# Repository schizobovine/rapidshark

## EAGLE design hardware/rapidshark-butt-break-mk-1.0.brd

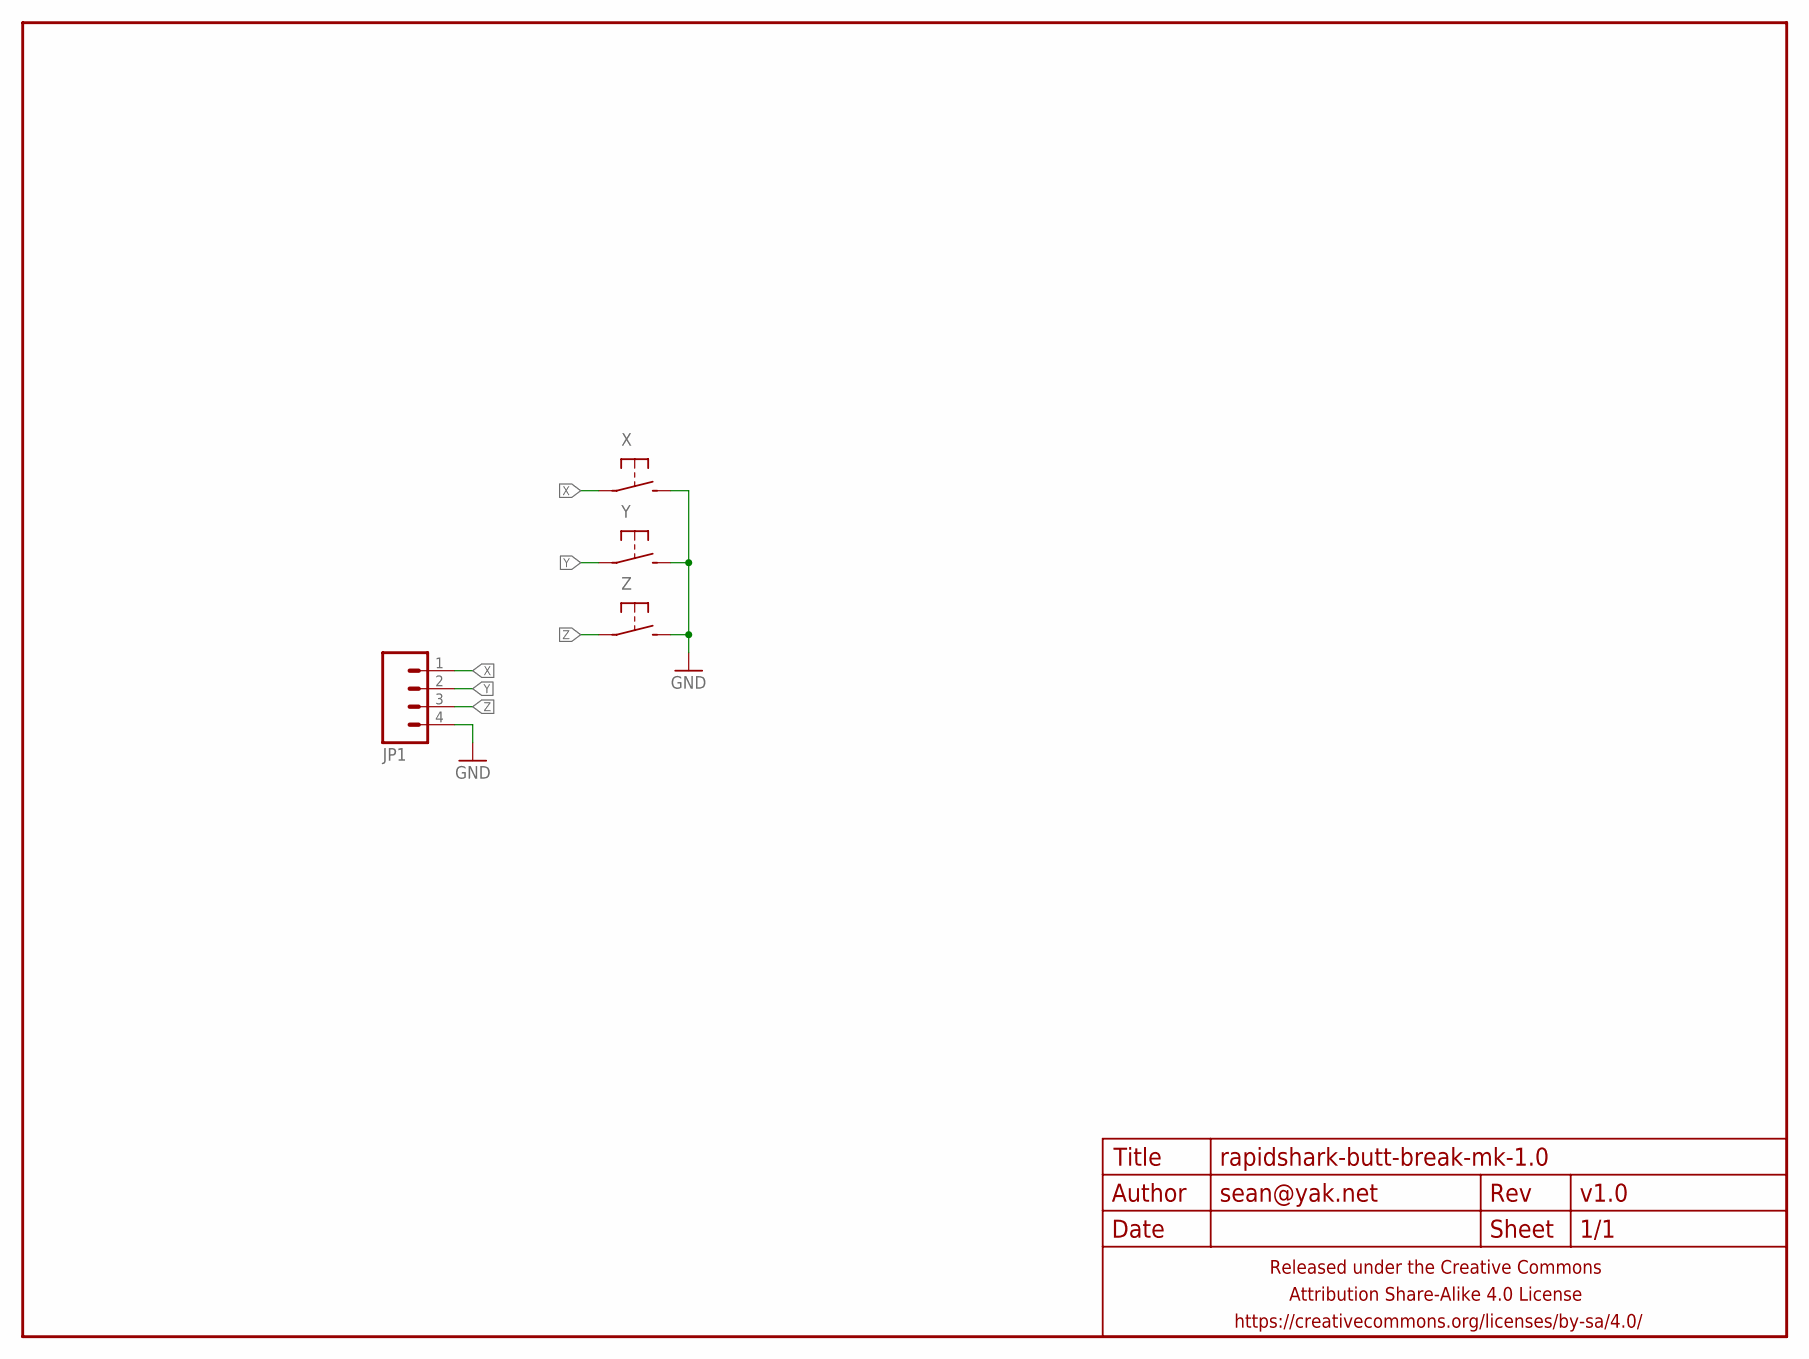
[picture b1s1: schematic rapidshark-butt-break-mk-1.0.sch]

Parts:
FRAME1: FRAME-LETTERNO_PACKAGE; DUMMY
JP1: M04JST-PTH; JST-4-PH-RA-PTH
X: SPST-NO-TACT3MM-PTH-SMALL-PADS; DTS-3-SMALL-PADS
Y: SPST-NO-TACT3MM-PTH-SMALL-PADS; DTS-3-SMALL-PADS
Z: SPST-NO-TACT3MM-PTH-SMALL-PADS; DTS-3-SMALL-PADS

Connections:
GND: JP1.4, X.2, Y.2, Z.2
X: JP1.1, X.1
Y: JP1.2, Y.1
Z: JP1.3, Z.1

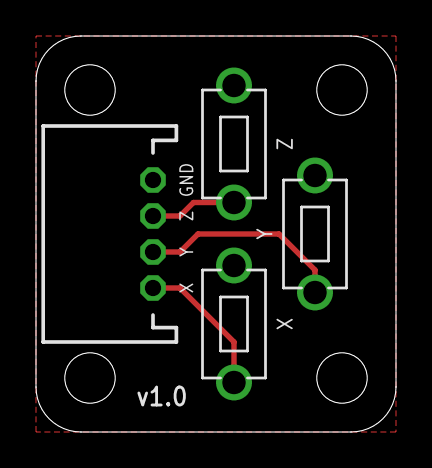
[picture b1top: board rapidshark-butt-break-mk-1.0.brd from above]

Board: 2 copper layers, 20.0 x 22.0 mm, 5 parts (1 on the bottom side), 4 nets.

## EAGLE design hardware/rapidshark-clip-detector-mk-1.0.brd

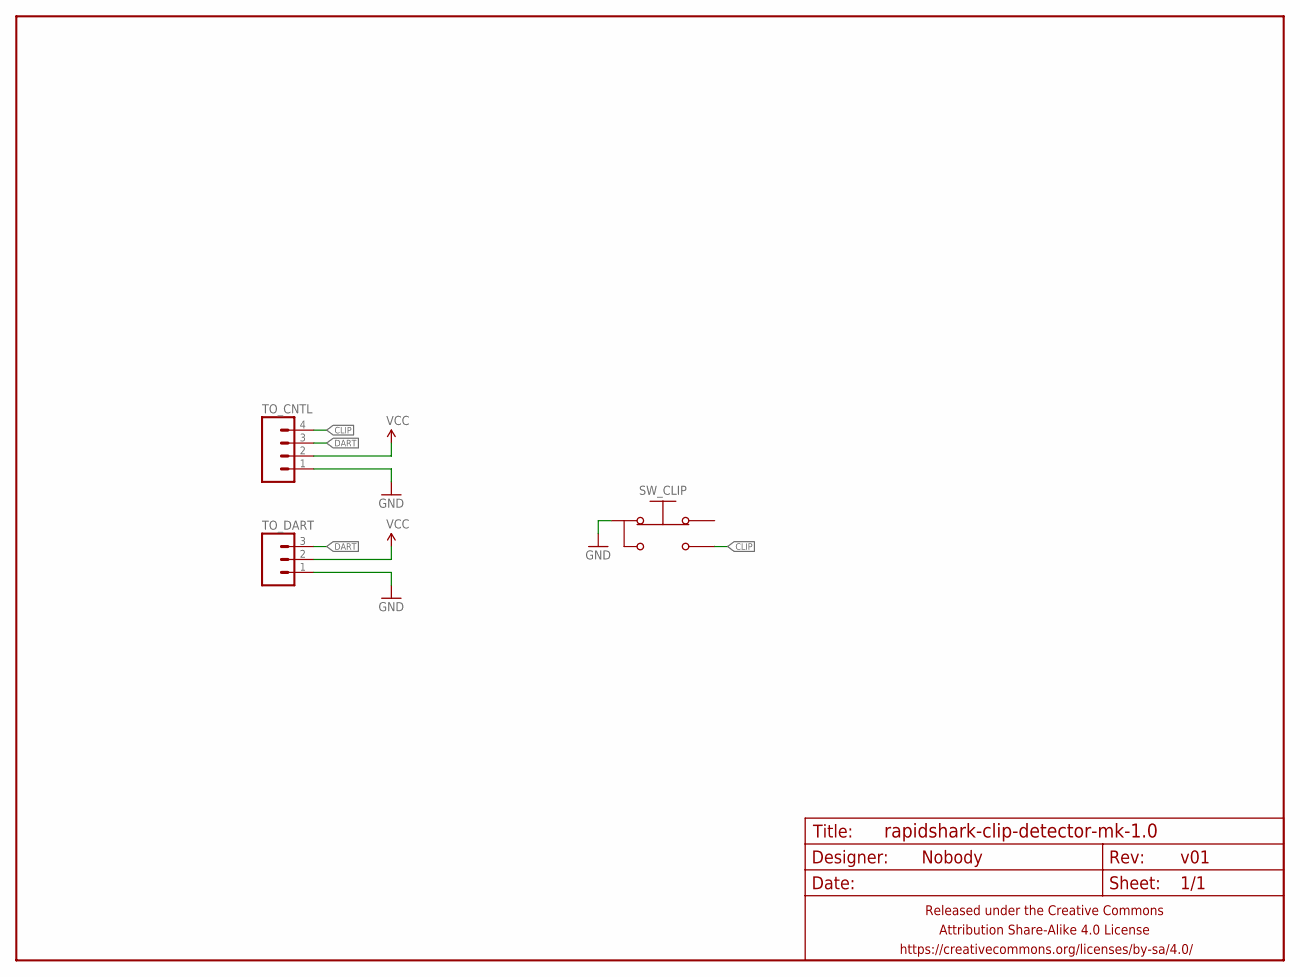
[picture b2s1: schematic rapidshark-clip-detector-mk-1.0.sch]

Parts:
FRAME1: FRAME-LETTERNO_PACKAGE; DUMMY
SW_CLIP: SPDT-NO-TACTPTH-RA-DETECT-3MM; SWITCH-DETECH-SPDT-3MM
TO_CNTL: M04JST-PTH-VERT; JST-4-PH-VERT-PTH
TO_DART: M03JST-PTH-VERT; JST-3-PH-VERT-PTH

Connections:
CLIP: SW_CLIP.3 (NO), TO_CNTL.4
DART: TO_CNTL.3, TO_DART.3
GND: SW_CLIP.2 (COM), TO_CNTL.1, TO_DART.1
VCC: TO_CNTL.2, TO_DART.2

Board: 2 copper layers, 4 parts (2 on the bottom side), 4 nets, no tracks yet.

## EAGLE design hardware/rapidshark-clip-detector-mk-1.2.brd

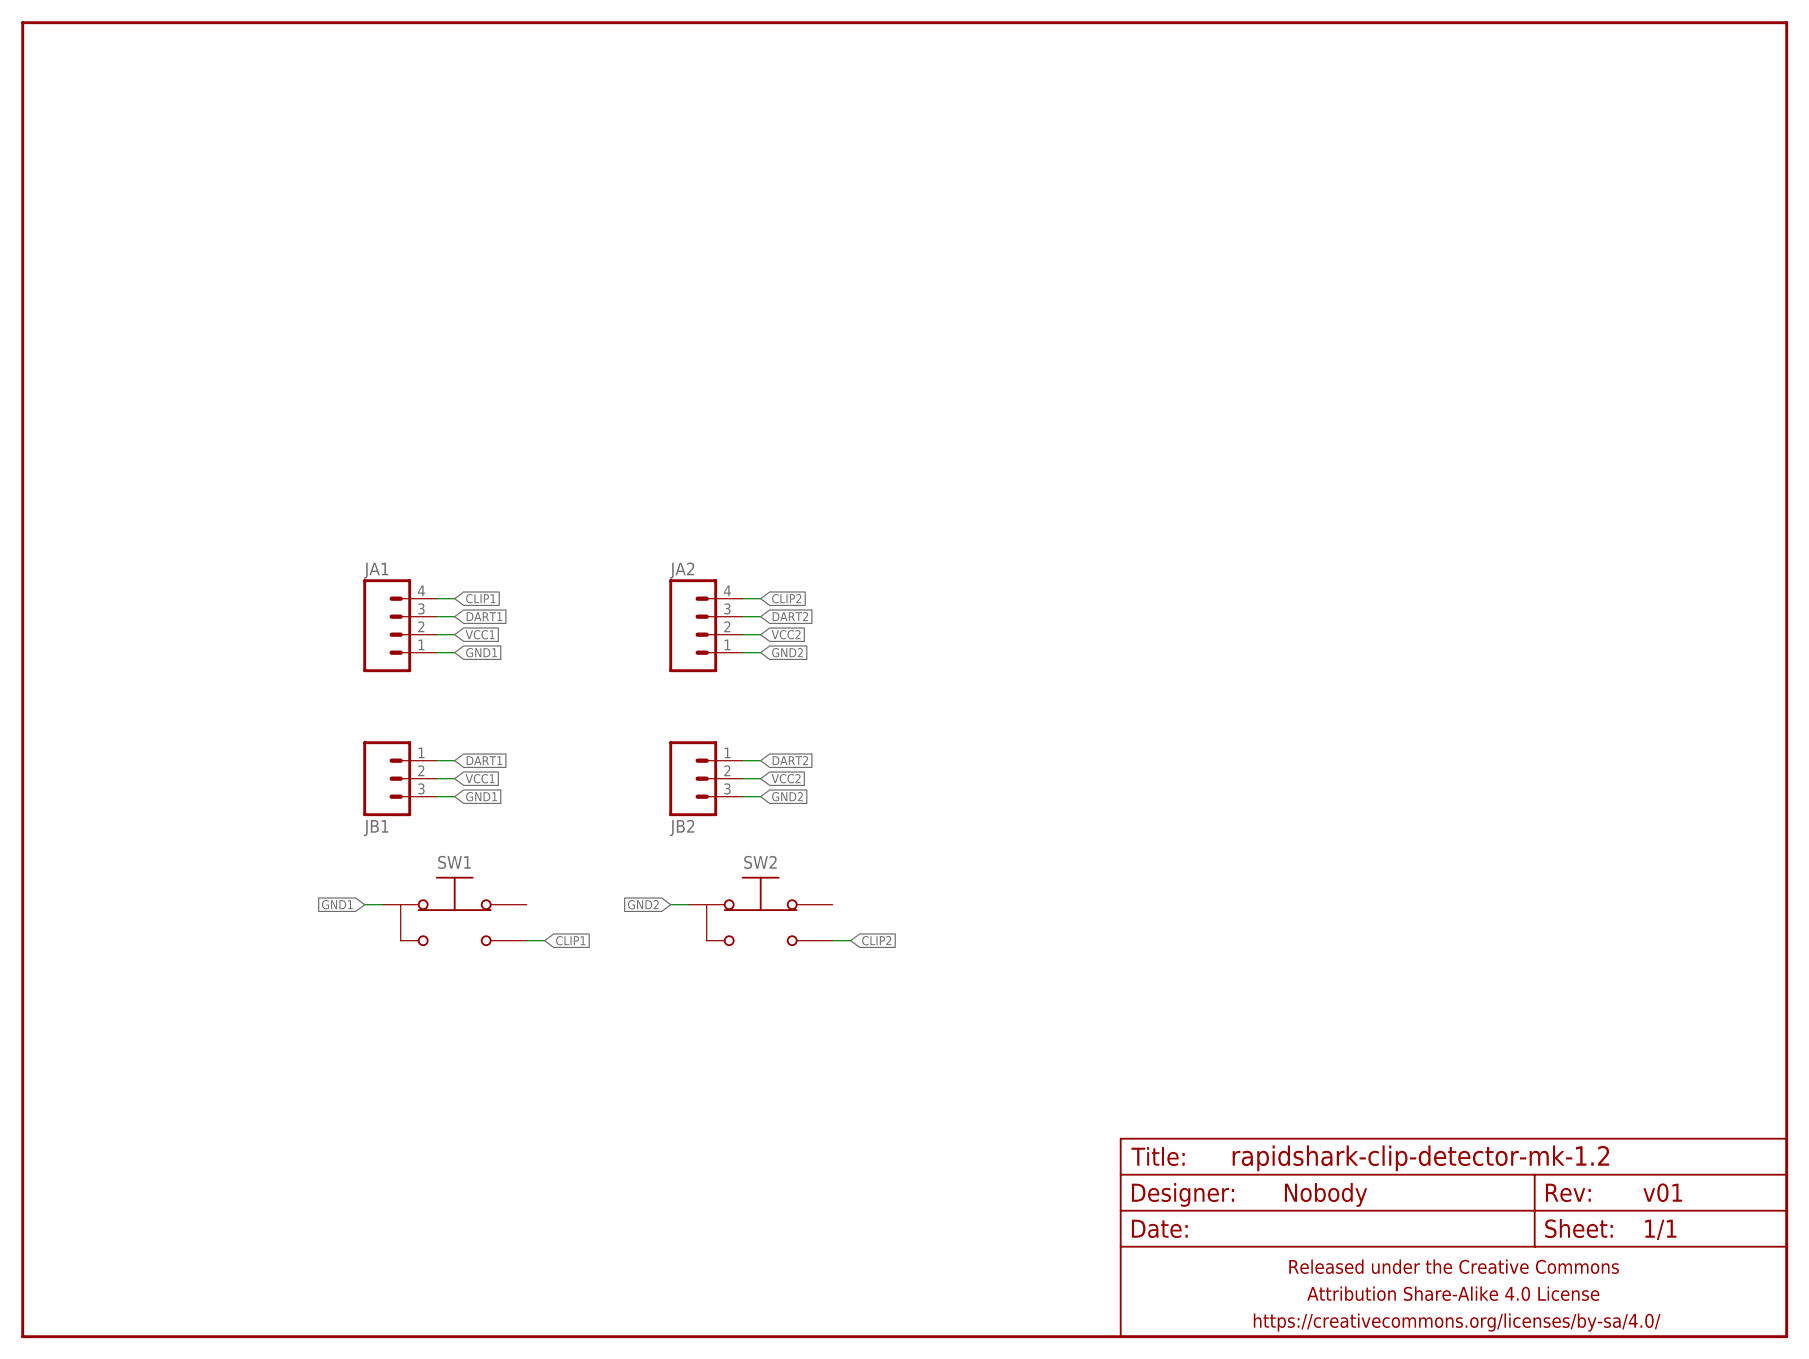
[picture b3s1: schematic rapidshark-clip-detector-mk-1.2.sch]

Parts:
FRAME1: FRAME-LETTERNO_PACKAGE; DUMMY
JA1, JA2: M04JST-PTH-VERT; JST-4-PH-VERT-PTH
JB1, JB2: M03JST-PTH-VERT; JST-3-PH-VERT-PTH
SW1, SW2: SPDT-NO-TACTPTH-RA-DETECT-3MM; SWITCH-DETECH-SPDT-3MM

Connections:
CLIP1: JA1.4, SW1.3 (NO)
CLIP2: JA2.4, SW2.3 (NO)
DART1: JA1.3, JB1.1
DART2: JA2.3, JB2.1
GND1: JA1.1, JB1.3, SW1.2 (COM)
GND2: JA2.1, JB2.3, SW2.2 (COM)
VCC1: JA1.2, JB1.2
VCC2: JA2.2, JB2.2

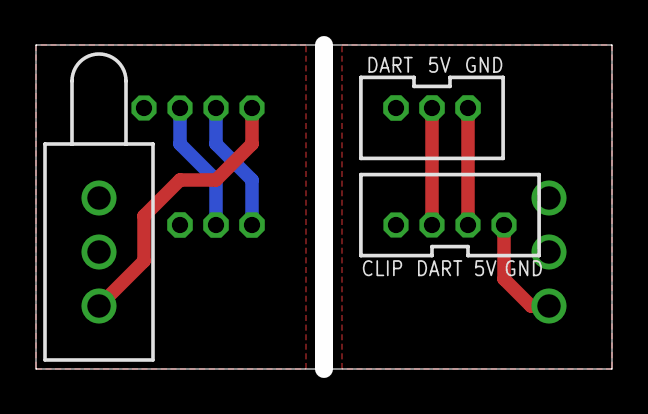
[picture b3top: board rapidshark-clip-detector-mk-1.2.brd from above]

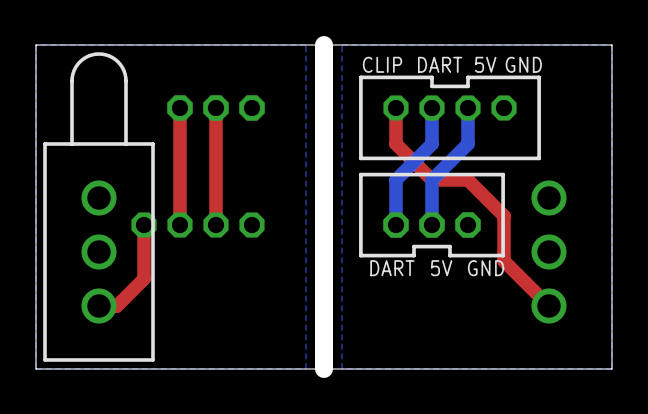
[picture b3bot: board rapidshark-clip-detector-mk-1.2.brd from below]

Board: 2 copper layers, 32.0 x 18.0 mm, 7 parts (4 on the bottom side), 8 nets.

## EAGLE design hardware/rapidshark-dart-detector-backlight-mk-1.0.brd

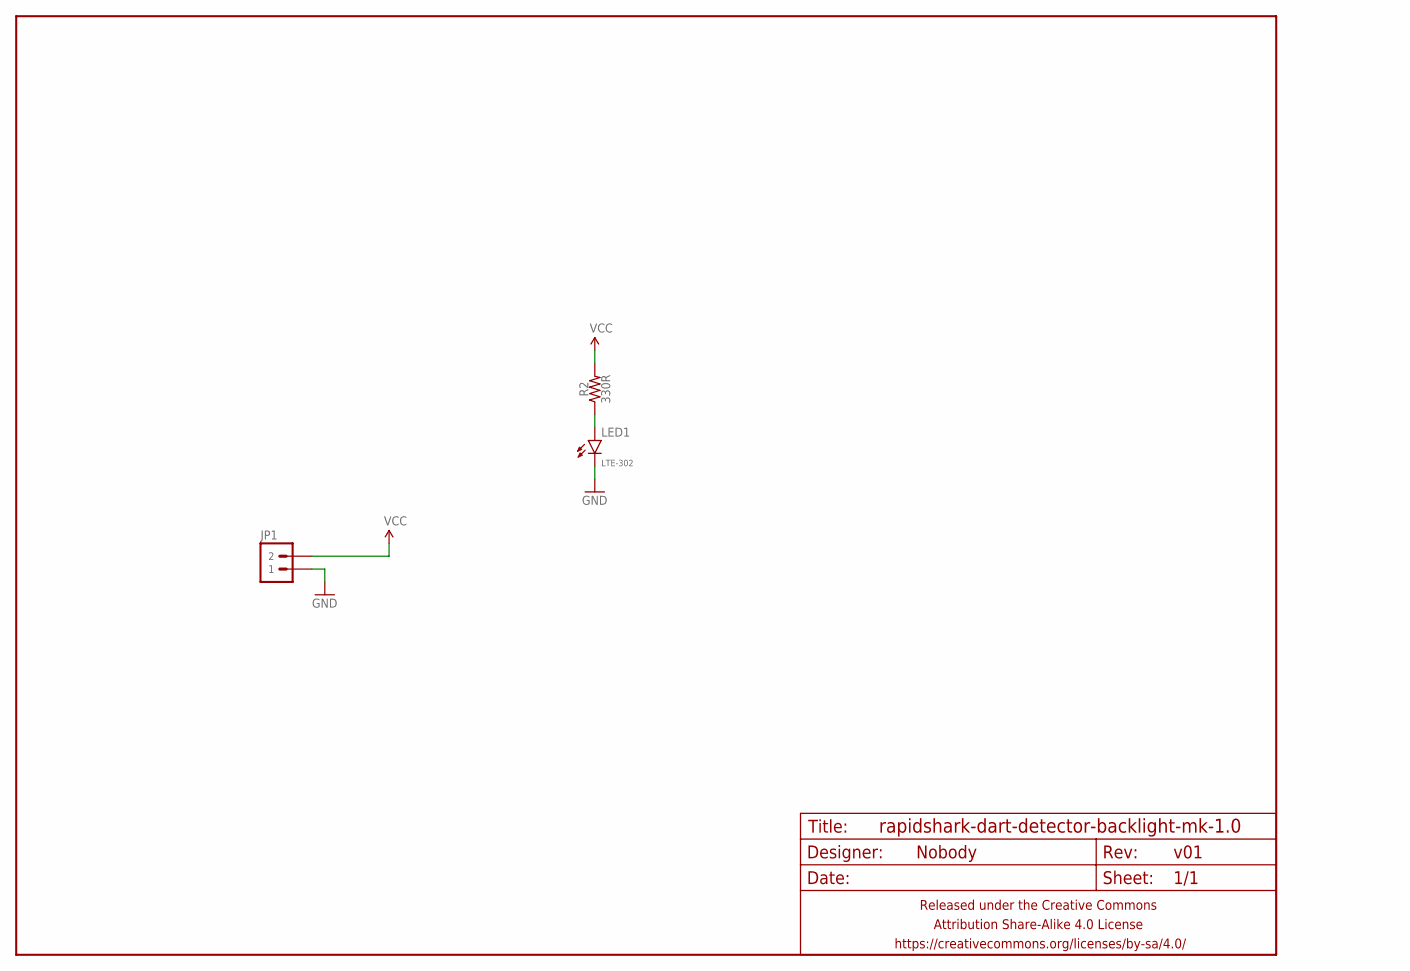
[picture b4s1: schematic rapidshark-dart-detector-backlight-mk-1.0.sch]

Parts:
FRAME1: FRAME-LETTERNO_PACKAGE; DUMMY
JP1: M02JST-PTH-RA-R+; JST-2-PH-RA-PTH-R+
LED1: LTE-302; LED-2.54MM-SIDE
R2: 330R; RESISTOR-AXIAL-PTH-7.62MM

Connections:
GND: JP1.1, LED1.K (C)
unnamed: LED1.A, R2.P$1 (1)
VCC: JP1.2, R2.P$2 (2)

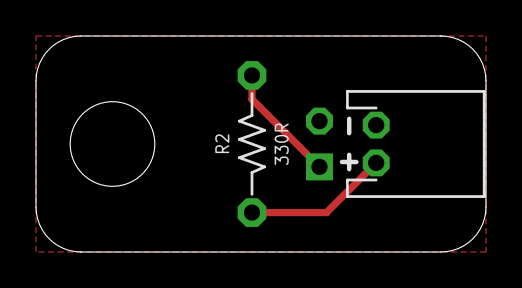
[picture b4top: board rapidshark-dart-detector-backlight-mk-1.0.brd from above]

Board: 2 copper layers, 25.0 x 12.0 mm, 4 parts (1 on the bottom side), 3 nets.

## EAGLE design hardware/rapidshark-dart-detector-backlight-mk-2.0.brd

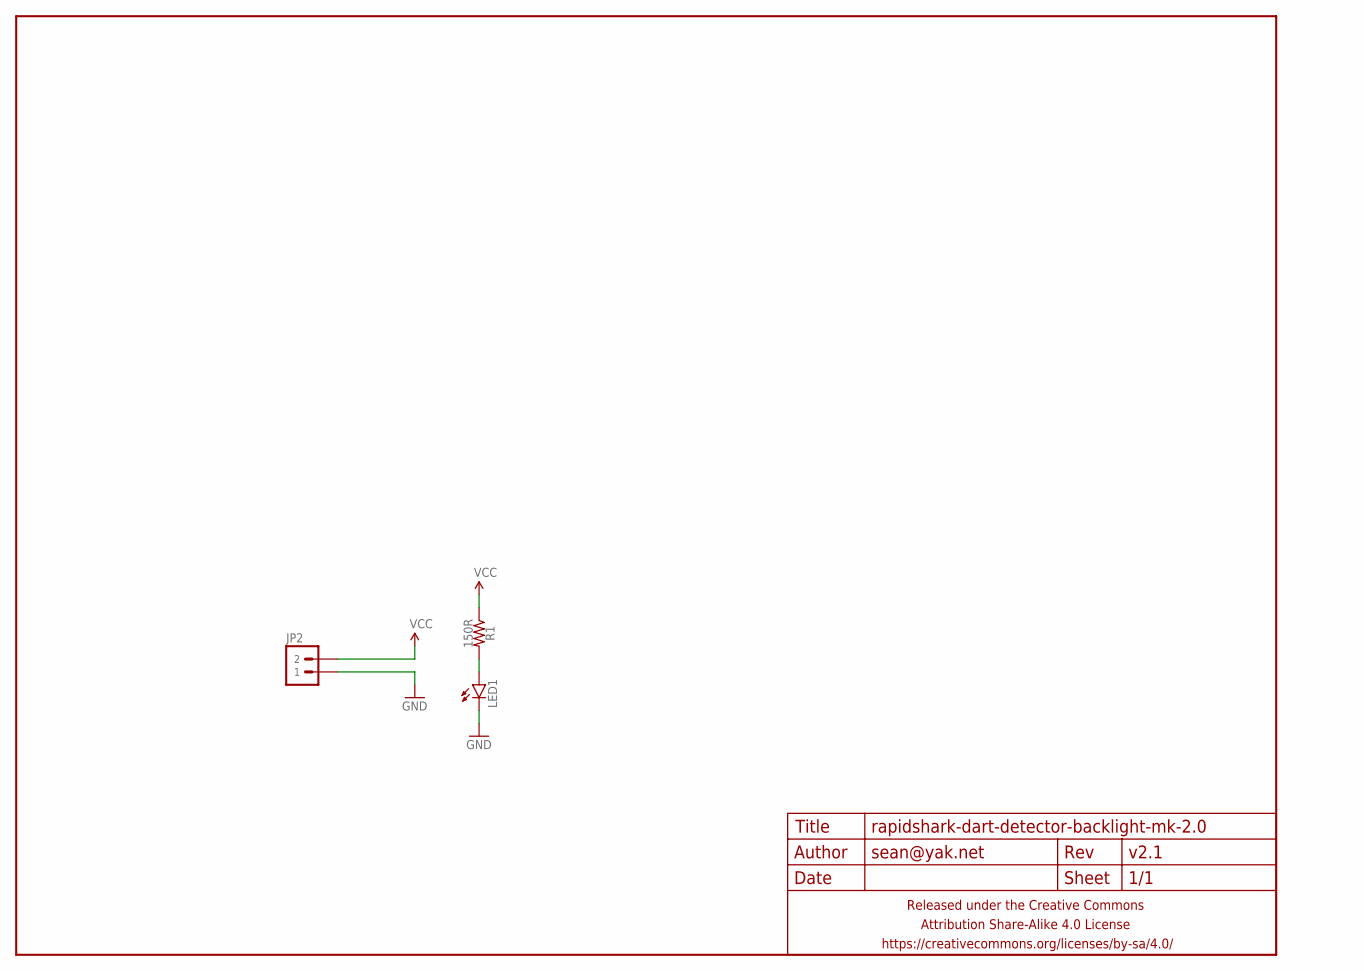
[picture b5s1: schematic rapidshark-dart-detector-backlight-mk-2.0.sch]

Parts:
FRAME1: FRAME-LETTERNO_PACKAGE; DUMMY
JP2: M02JST-PTH-RA-R+; JST-2-PH-RA-PTH-R+
LED1: LED5MM_SHORTPADS
R1: 150R; RESISTOR-AXIAL-PTH-6.35MM

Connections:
GND: JP2.1, LED1.K (C)
unnamed: LED1.A, R1.P$2 (2)
VCC: JP2.2, R1.P$1 (1)

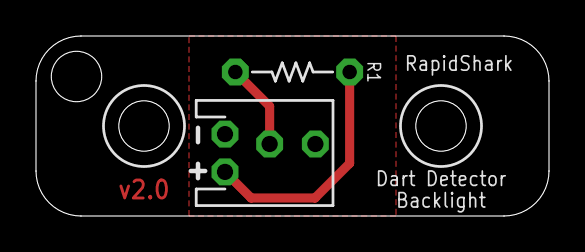
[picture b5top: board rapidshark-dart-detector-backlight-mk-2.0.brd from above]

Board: 2 copper layers, 28.5 x 10.0 mm, 4 parts (1 on the bottom side), 3 nets.

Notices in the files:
parts and their libraries:
A_butts: Released under the Creative Commons Attribution Share-Alike 4.0 License
A_butts: https://creativecommons.org/licenses/by-sa/4.0
A_butts: Released under the Creative Commons
